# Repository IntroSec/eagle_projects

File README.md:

# eagle_designs
Our Schematic and PCB design files with Eagle PCB CAD software.

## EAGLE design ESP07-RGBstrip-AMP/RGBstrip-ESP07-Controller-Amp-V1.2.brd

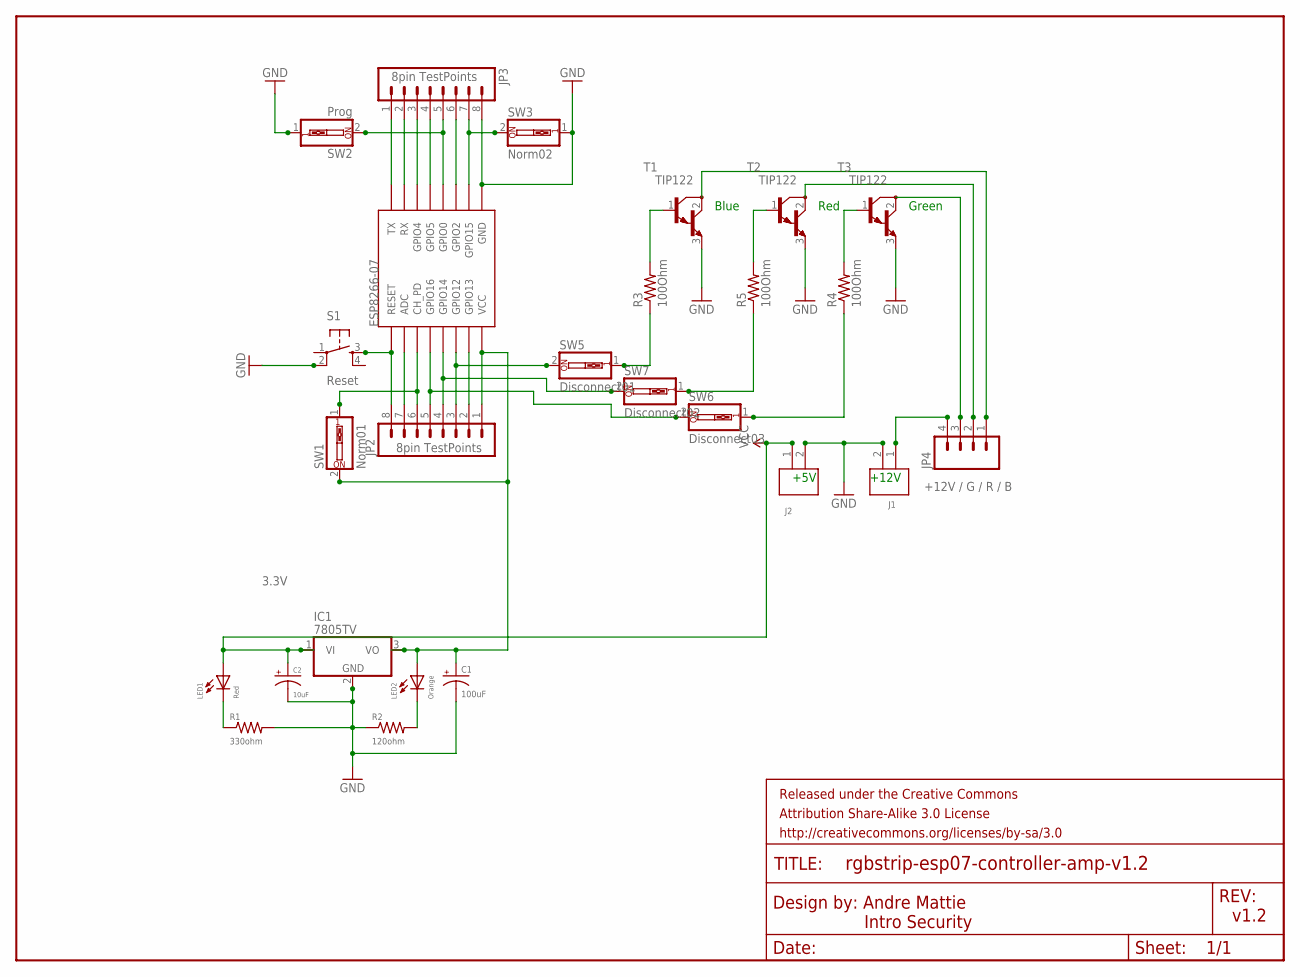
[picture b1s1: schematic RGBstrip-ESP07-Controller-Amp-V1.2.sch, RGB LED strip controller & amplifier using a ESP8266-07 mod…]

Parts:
C1: 100uF; CPOL-RADIAL-100UF-25V
C2: 10uF; CPOL-RADIAL-10UF-25V
ESP8266-07: ESP07-16PINBOTTOM; ESP07-16PIN
FRAME1: FRAME-LETTER; CREATIVE_COMMONS
IC1: 7805TV; TO220V
J1, J2: SCREW-TERMINAL_2_0.100; CONN_BLOCK_2
JP2, JP3: 8pin TestPoints; 1X08_LONGPADS
JP4: +12V / G / R / B; 1X04_LONGPADS
LED1: Red; LED3MM
LED2: Orange; LED3MM
R1: 330ohm; 0309V
R2: 120ohm; 0309V
R3, R4, R5: 100Ohm; 0309V
S1: Reset; TACTILE-PTH
SW1: Norm01; EDG-01
SW2: Prog; EDG-01
SW3: Norm02; EDG-01
SW5: Disconnect01; EDG-01
SW6: Disconnect03; EDG-01
SW7: Disconnect02; EDG-01
T1, T2, T3: TIP122; TO220

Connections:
3.3V: C1.1 (+), ESP8266-07.VCC, IC1.3 (VO), JP2.1, LED2.A, SW1.2
BLUE-SUPPLY: JP4.1, T1.2 (C)
GND: C1.2 (-), C2.2 (-), ESP8266-07.GND, IC1.2 (GND), J1.2, J2.2, JP3.8, R1.2, R2.1, S1.2, SW2.1, SW3.1, T1.3 (E), T2.3 (E), T3.3 (E)
GREEN: ESP8266-07.GPIO16, JP2.5, SW6.2
GREEN-SUPPLY: JP4.3, T3.2 (C)
unnamed: ESP8266-07.TX, JP3.1
unnamed: ESP8266-07.GPIO15, JP3.7, SW3.2
unnamed: LED1.K (C), R1.1
unnamed: LED2.K (C), R2.2
unnamed: ESP8266-07.CH_PD, JP2.6, SW1.1
unnamed: R3.1, SW5.1
unnamed: R4.1, SW6.1
unnamed: ESP8266-07.RX, JP3.2
unnamed: ESP8266-07.GPIO0, JP3.5, SW2.2
unnamed: R3.2, T1.1 (B)
unnamed: R5.1, SW7.1
unnamed: ESP8266-07.GPIO4, JP3.3
unnamed: ESP8266-07.GPIO5, JP3.4
unnamed: ESP8266-07.GPIO2, JP3.6
unnamed: ESP8266-07.REST (RESET), JP2.8, S1.3
unnamed: R5.2, T2.1 (B)
unnamed: J1.1, JP4.4
unnamed: R4.2, T3.1 (B)
unnamed: ESP8266-07.ADC, JP2.7
unnamed: ESP8266-07.GPIO12, JP2.3, SW5.2
unnamed: ESP8266-07.GPIO13, JP2.2
RED: ESP8266-07.GPIO14, JP2.4, SW7.2
RED-SUPPLY: JP4.2, T2.2 (C)
VCC: C2.1 (+), IC1.1 (VI), J2.1, LED1.A

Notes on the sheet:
v1.2
+5V
+12V
Green
Red
Blue

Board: 2 copper layers, 31 parts (2 on the bottom side), 29 nets, no tracks yet.

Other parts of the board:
U$1, U$2, U$3, U$4: 3,3

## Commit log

2016-10-03 Updated LICENSE
2016-10-06 added new schematic and board for RGB LED controller/amplifier
2016-10-06 added V1.2 schematic and board which replaces 2pin jumpers with single dip switches

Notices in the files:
parts and their libraries:
SparkFun-Capacitors: Licensing: CC v3.0 Share-Alike You are welcome to use this library for commercial purposes.
Aesthetics: Released under the Creative Commons Attribution Share-Alike 3.0 License
Aesthetics: http://creativecommons.org/licenses/by-sa/3.0
